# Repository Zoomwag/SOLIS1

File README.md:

<div align="center">

# Solis 1 CanSat

</div>

---

## About

**Solis 1** is my custom-built CanSat project, designed to fit all the main systems of a small satellite inside a compact cylindrical enclosure.

The CanSat measures approximately:

* **64 mm in diameter**
* **110 mm tall**

The project includes a custom flight computer PCB, a lightweight enclosure, onboard software, a recovery system and a ground station.

The aim of Solis 1 is to create a compact and system that can collect data during a test flight, transmit information back to the ground and safely return for recovery.

---

## Project Goals

The main goals of the project are to:

* Design a fully custom flight computer
* Fit the complete system inside the CanSat enclosure
* Collect and store flight data
* Transmit data to a ground station
* Create a lightweight but strong structure
* Test the CanSat through multiple ground and flight tests
* Learn more about PCB design, electronics, programming and engineering

---

## CanSat Design

The outside structure is designed to protect the electronics while keeping the CanSat lightweight and easy to assemble.

The design includes mounting points for the flight computer, battery and other internal parts. It will also allow the CanSat to be opened for maintenance, testing and repairs.

<!-- Add an image or render of the complete CanSat here -->

---

## Flight Computer PCB

The Solis 1 flight computer is a custom PCB designed specifically for this project.

It will connect the main electronics together and reduce the amount of loose wiring inside the CanSat. The PCB is being designed to be compact, organised and easy to test.

<!-- Add a PCB render or photograph here -->

---

## PCB Schematic

The schematic shows how the components  on the flight computer are connected together

---

## PCB Layout

The board is designed to fit inside the Solis 1 enclosure while leaving enough space for mounting holes, connectors and other internal parts.

I even included some really nice graphics on the back

---

## BOM

Here you can see the bom for Solis 1

---

## Mechanical Design

This includes the outer enclosure, internal mounts, PCB supports and recovery-system parts. The design needs to be compact, lightweight and strong enough to protect the electronics during testing and landing.

---

---
#Images

theses are the pcb boards for solis 1 you can see the mother board and the daughter board. You can also see the very nice silkscreen :)

this was when i wired them together

here are the electronics inside of the enclosure

here is everyting wiht the lid on
---

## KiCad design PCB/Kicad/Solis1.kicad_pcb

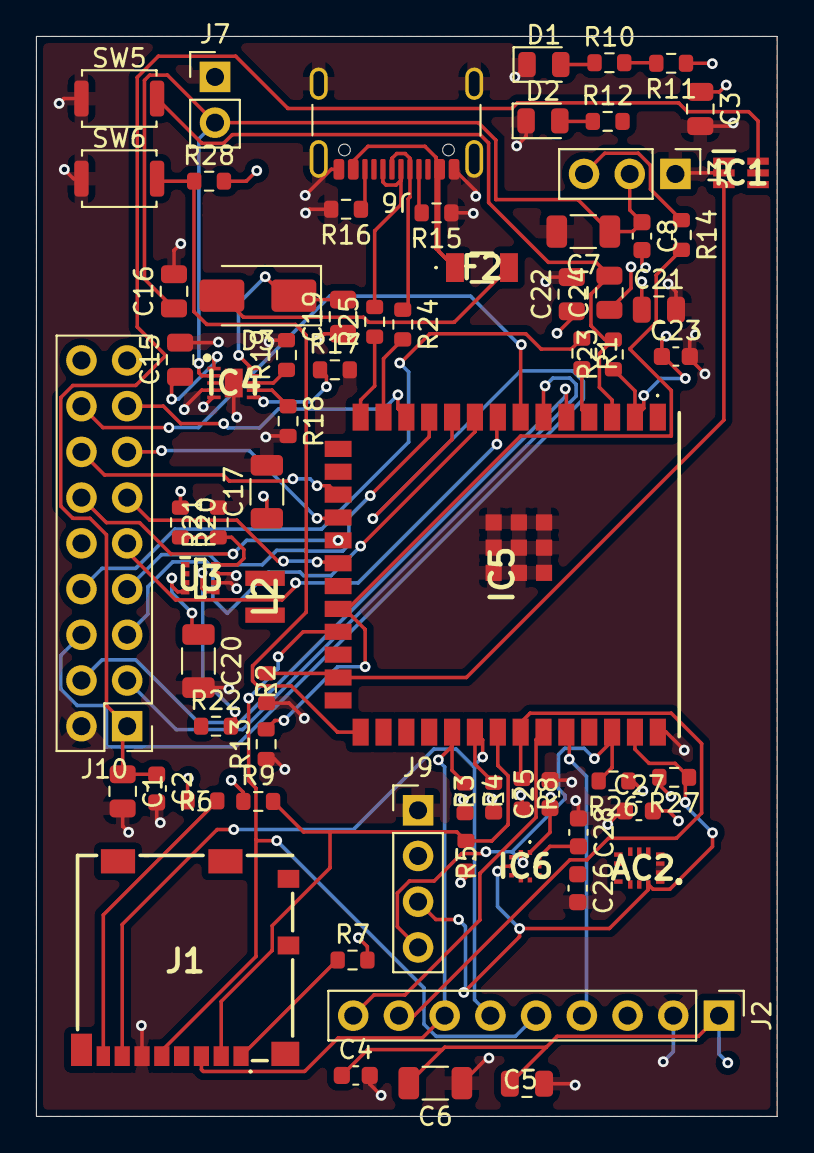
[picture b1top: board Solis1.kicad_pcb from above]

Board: 4 copper layers, 41.2 x 60.0 mm, 69 parts (0 on the bottom side), 55 nets.

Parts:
AC2: LSM6DSOTR; LSM6DS3USTR
C1, C5, C15, C22: 10uF; C_0805_2012Metric
C2, C4, C8, C23, C25, C26, C27, C28: 100nF; C_0603_1608Metric
C3, C21, C24: 1uF; C_0805_2012Metric
C6, C17: 47uF; C_1206_3216Metric
C7: 470uF; C_1206_3216Metric
C16, C19: 2.2uF; C_0805_2012Metric
C20: 22uF; C_1206_3216Metric
D1, D2: LED; LED_0805_2012Metric
D3: SS14-E3/5AT; D_SMA
F2: MF-NSMF075_8X-2; MFNSMF0758X2
IC1: TPS22919DCKT; SOT65P210X110-6N
IC4: BQ25185DLHR; SON40P220X200X80-11N
IC5: ESP32-S3-WROOM-1U-N16R8; ESP32S3WROOM1UN16R8
IC6: BMP390
J1: Micro_SD_Card_Det1; 1040310811
J2: LORA MODULE; PinHeader_1x09_P2.54mm_Vertical
J3: Conn_01x03_Pin; PinHeader_1x03_P2.54mm_Vertical
J6: USB_C_Receptacle_USB2.0_16P; USB_C_Receptacle_GCT_USB4105-xx-A_16P_TopMnt_Horizontal
J7: Battery; PinHeader_1x02_P2.54mm_Vertical
J9: Conn_01x04_Socket; PinHeader_1x04_P2.54mm_Vertical
J10: Camera; PinHeader_2x09_P2.54mm_Vertical
L2: 1uH; DFE2HCAH1R0MJ0L
R1, R24, R25: 22; R_0603_1608Metric
R2, R13, R22: 100K; R_0603_1608Metric
R3, R4, R5, R6, R7, R8, R9, R10, R17, R23, R28: 10K; R_0603_1608Metric
R11: 0; R_0603_1608Metric
R12, R26, R27: 4.7K; R_0603_1608Metric
R14: 220; R_0603_1608Metric
R15, R16: 5.1K; R_0603_1608Metric
R18: 18K; R_0603_1608Metric
R19: 1K; R_0603_1608Metric
R20: 511K; R_0603_1608Metric
R21: 91K; R_0603_1608Metric
SW5, SW6: SW_Push; SW_Push_SPST_NO_Alps_SKRK
U3: TPS631000DRLR; SOTFL50P160X60-8N

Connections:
+3V3: AC2.5 (VDDIO), AC2.8 (VDD), AC2.12 (CS), C3.1, C4.1, C5.1, C6.2, C17.1, C21.1, C22.1, C23.1, C25.1, C26.1, C27.2, C28.2, IC1.1 (IN), IC5.2 (3V3), IC6.1 (VDDIO), IC6.6 (CSB), IC6.10 (VDD), J1.4 (VDD), J2.1, J9.2, R3.2, R4.2, R5.1, R6.1, R7.2, R8.2, R9.1, R11.1, R20.1, R23.1, R26.1, R27.2, R28.2, U3.1 (VOUT)
/CAM_3V3: C1.1, C2.1, IC1.5 (QOD), IC1.6 (OUT), J10.1, R12.2
/CAM_PWR: IC1.3 (ON), IC5.25 (IO48), R2.1
/CHARGER_IN: C19.2, D3.1 (K), IC4.10 (IN)
/Camera_D0: IC5.7 (IO7), J10.16
/Camera_D1: IC5.12 (IO8), J10.15
/Camera_D2: IC5.17 (IO9), J10.14
/Camera_D3: IC5.18 (IO10), J10.13
/Camera_D4: IC5.19 (IO11), J10.12
/Camera_D5: IC5.20 (IO12), J10.11
/Camera_D6: IC5.21 (IO13), J10.10
/Camera_D7: IC5.8 (IO15), J10.9
/Camera_HREF: IC5.10 (IO17), J10.6
/Camera_PCLK: IC5.11 (IO18), J10.7
/Camera_SCCB_SCL: IC5.6 (IO6), J10.3
/Camera_SCCB_SDA: IC5.5 (IO5), J10.4
/Camera_VSYNC: IC5.9 (IO16), J10.5
/Camera_XCLK: IC5.4 (IO4), R1.2
/LORA_CS: IC5.34 (IO41), J2.8, R8.1
/LORA_DIO0: IC5.36 (RXD0), J2.4
/LORA_RST: IC5.35 (IO42), J2.9
/SD_CS: IC5.33 (IO40), J1.2 (DAT3/CD), R5.2, R9.2
/SPI_MISO: IC5.32 (IO39), J1.7 (DAT0), J2.6, R4.1
/SPI_MOSI: IC5.31 (IO38), J1.3 (CMD), J2.7, R3.1
/SPI_SCK: IC5.23 (IO21), J1.5 (CLK), J2.5
/SYS_RAW: C15.1, C20.1, IC4.1 (SYS), R22.1, U3.4 (VIN)
/Sensor_I²C_SCL: AC2.13 (SCL), IC5.38 (IO2), IC6.2 (SCK), J9.4, R26.2
/Sensor_I²C_SDA: AC2.14 (SDA), IC5.39 (IO1), IC6.4 (SDI), J9.3, R27.1
/Servo1_PWM: IC5.22 (IO14), R13.2, R14.2
/USB_D+: J6.A6 (D+), J6.B6 (D+), R25.2
/USB_D-: J6.A7 (D-), J6.B7 (D-), R24.1
/USB_FUSED: D3.2 (A), F2.2
/USB_VBUS: F2.1, J6.A4 (VBUS), J6.A9 (VBUS), J6.B4 (VBUS), J6.B9 (VBUS)
/VBAT: C7.1, C8.1, C16.1, IC4.2 (BAT), J3.2, J7.2
GND: AC2.1 (SDO/SA0), AC2.2 (SDX), AC2.3 (SCX), AC2.6 (GND_1), AC2.7 (GND_2), C1.2, C2.2, C3.2, C4.2, C5.2, C6.1, C7.2, C8.2, C15.2, C16.2, C17.2, C19.1, C20.2, C21.2, C22.2, C23.2, C24.1, C25.2, C26.2, C27.1, C28.1, D1.1 (K), D2.1 (K), IC1.2 (GND), IC4.4 (~CE), IC4.5 (GND), IC4.11 (EP), IC5.1 (GND_1), IC5.40 (GND_2), IC5.41 (GND_3), IC5.42 (GND_4), IC5.43 (GND_5), IC5.44 (GND_6), IC5.45 (GND_7), IC5.46 (GND_8), IC5.47 (GND_9), IC5.48 (GND_10), IC5.49 (GND_11), IC6.3 (VSS_1), IC6.5 (SDO), IC6.8 (VSS_2), IC6.9 (VSS_3), J1.6 (VSS), J2.2, J3.1, J6.A1 (GND), J6.A12 (GND), J6.B1 (GND), J6.B12 (GND), J6.SH (SHIELD), J7.1, J9.1, J10.2, R2.2, R13.1, R15.1, R16.2, R17.2, R18.2, R19.2, R21.2, SW5.1, SW6.1, U3.6 (MODE), U3.7 (GND)
unnamed: D1.2 (A), R10.1
unnamed: D2.2 (A), R12.1
unnamed: IC4.7 (ILIM/VSET), R18.1
unnamed: IC4.8 (ISET), R19.1
unnamed: IC4.6 (TS/MR), R17.1
unnamed: C24.2, IC5.3 (EN), R23.2, SW5.2
unnamed: IC5.27 (IO0), R28.1, SW6.2
unnamed: IC5.13 (IO19), R24.2
unnamed: IC5.14 (IO20), R25.1
unnamed: J1.8 (DAT1), R6.2
unnamed: J1.1 (DAT2), R7.1
unnamed: J3.3, R14.1
unnamed: J6.A5 (CC1), R15.2
unnamed: J6.B5 (CC2), R16.1
unnamed: J10.8, R1.1
unnamed: R10.2, R11.2
unnamed: R22.2, U3.5 (EN)
unnamed: R20.2, R21.1, U3.8 (FB)
unnamed: L2.1, U3.3 (LX1)
unnamed: L2.2, U3.2 (LX2)

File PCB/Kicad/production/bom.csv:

Designator,Footprint,Quantity,Value,LCSC Part #
AC2,LSM6DS3USTR,1,LSM6DSOTR,
"C1, C15, C18, C22, C5",0805,5,10uF,
"C16, C19",0805,2,2.2uF,
"C17, C6",1206,2,47uF,
"C2, C23, C25, C26, C27, C28, C4, C8",0603,8,100nF,
C20,1206,1,22uF,
"C21, C24, C3",0805,3,1uF,
C7,1206,1,470uF,
"D1, D2",0805,2,LED,
"D3, D4",D_SMA,2,SS14-E3/5AT,
F2,MFNSMF0758X2,1,MF-NSMF075_8X-2,
IC1,SOT65P210X110-6N,1,TPS22919DCKT,
IC4,SON40P220X200X80-11N,1,BQ25185DLHR,
IC5,ESP32S3WROOM1UN16R8,1,ESP32-S3-WROOM-1U-N16R8,
IC6,BMP390,1,BMP390,
J1,1040310811,1,Micro_SD_Card_Det1,
J10,PinHeader_2x09_P2.54mm_Vertical,1,Camera,
J2,PinHeader_1x09_P2.54mm_Vertical,1,LORA MODULE,
J3,PinHeader_1x03_P2.54mm_Vertical,1,Conn_01x03_Pin,
J6,USB_C_Receptacle_GCT_USB4105-xx-A_16P_TopMnt_Horizontal,1,USB_C_Receptacle_USB2.0_16P,
J7,PinHeader_1x02_P2.54mm_Vertical,1,Battery,
J9,PinHeader_1x04_P2.54mm_Vertical,1,Conn_01x04_Socket,
L2,DFE2HCAH1R0MJ0L,1,1uH,
"R1, R24, R25",0603,3,22,
"R10, R17, R23, R28, R3, R4, R5, R6, R7, R8, R9",0603,11,10K,
R11,0603,1,0,
"R12, R26, R27",0603,3,4.7K,
"R13, R2, R22",0603,3,100K,
R14,0603,1,220,
"R15, R16",0603,2,5.1K,
R18,0603,1,18K,
R19,0603,1,1K,
R20,0603,1,511K,
R21,0603,1,91K,
"SW5, SW6",SW_Push_SPST_NO_Alps_SKRK,2,SW_Push,
TP1,TestPoint_Pad_1.0x1.0mm,1,GND1,
TP2,TestPoint_Pad_1.0x1.0mm,1,TestPoint,
TP3,TestPoint_Pad_1.0x1.0mm,1,GND2,
TP4,TestPoint_Pad_1.0x1.0mm,1,VBAT,
TP5,TestPoint_Pad_1.0x1.0mm,1,SYS_SW,
TP6,TestPoint_Pad_1.0x1.0mm,1,3v3,
TP8,TestPoint_Pad_1.0x1.0mm,1,SDA,
TP9,TestPoint_Pad_1.0x1.0mm,1,SCL,
U3,SOTFL50P160X60-8N,1,TPS631000DRLR,
